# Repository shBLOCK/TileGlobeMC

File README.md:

# TileGlobeMC

-----

[Demo Video](https://youtu.be/YhDgAMrMPlI)

TODO: Description

Project Structure
-----
- tileglobe: game logic
- datagen/mod: a fabric modding environment for extracting/generating data from vanilla (e.g. blockstate info, networking packet IDs, etc.)
- tileglobe_pymeta: Python environment and helper package for [pymeta](https://github.com/shBLOCK/pymeta) usage in the project
- tileglobe_server: Minecraft server protocol implementation
- tileglobe_runtime: runtime platform implementation
  - pc
  - rp2350: runnable on a [Pimoroni Pico Plus 2 W](https://shop.pimoroni.com/en-us/products/pimoroni-pico-plus-2-w)

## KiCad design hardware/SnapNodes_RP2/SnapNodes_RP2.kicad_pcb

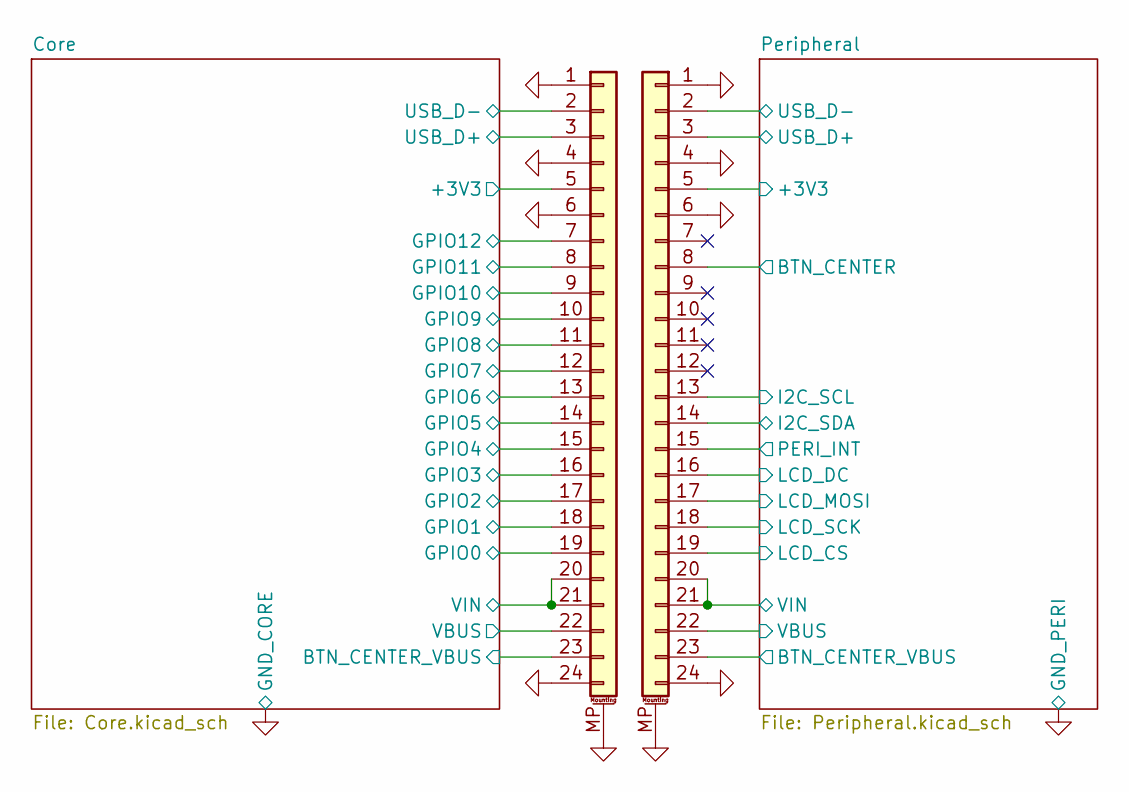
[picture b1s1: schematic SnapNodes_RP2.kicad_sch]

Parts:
J20, J21: Conn_01x24_MountingPin; FPC_Verticle_24pin_0.5mm

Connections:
+3V3: J20.5; also elsewhere on the board
/Core/BTN_CENTER_VBUS: J20.23; also elsewhere on the board
/Core/GPIO0: J20.19; also elsewhere on the board
/Core/GPIO1: J20.18; also elsewhere on the board
/Core/GPIO2: J20.17; also elsewhere on the board
/Core/GPIO3: J20.16; also elsewhere on the board
/Core/GPIO4: J20.15; also elsewhere on the board
/Core/GPIO5: J20.14; also elsewhere on the board
/Core/GPIO6: J20.13; also elsewhere on the board
/Core/GPIO7: J20.12; also elsewhere on the board
/Core/GPIO8: J20.11; also elsewhere on the board
/Core/GPIO9: J20.10; also elsewhere on the board
/Core/GPIO10: J20.9; also elsewhere on the board
/Core/GPIO11: J20.8; also elsewhere on the board
/Core/GPIO12: J20.7; also elsewhere on the board
/Core/USB_D+: J20.3; also elsewhere on the board
/Core/USB_D-: J20.2; also elsewhere on the board
/Core/VIN: J20.20, J20.21; also elsewhere on the board
/Peripheral/+3V3: J21.5; also elsewhere on the board
/Peripheral/BTN_CENTER: J21.8; also elsewhere on the board
/Peripheral/BTN_CENTER_VBUS: J21.23; also elsewhere on the board
/Peripheral/I2C_SCL: J21.13; also elsewhere on the board
/Peripheral/I2C_SDA: J21.14; also elsewhere on the board
/Peripheral/LCD_CS: J21.19; also elsewhere on the board
/Peripheral/LCD_DC: J21.16; also elsewhere on the board
/Peripheral/LCD_MOSI: J21.17; also elsewhere on the board
/Peripheral/LCD_SCK: J21.18; also elsewhere on the board
/Peripheral/PERI_INT: J21.15; also elsewhere on the board
/Peripheral/USB_D+: J21.3; also elsewhere on the board
/Peripheral/USB_D-: J21.2; also elsewhere on the board
/Peripheral/VBUS: J21.22; also elsewhere on the board
/Peripheral/VIN: J21.20, J21.21; also elsewhere on the board
GND_CORE: J20.1, J20.4, J20.6, J20.24, J20.MP (MountPin); also elsewhere on the board
GND_PERI: J21.1, J21.4, J21.6, J21.24, J21.MP (MountPin); also elsewhere on the board
VBUS: J20.22; also elsewhere on the board

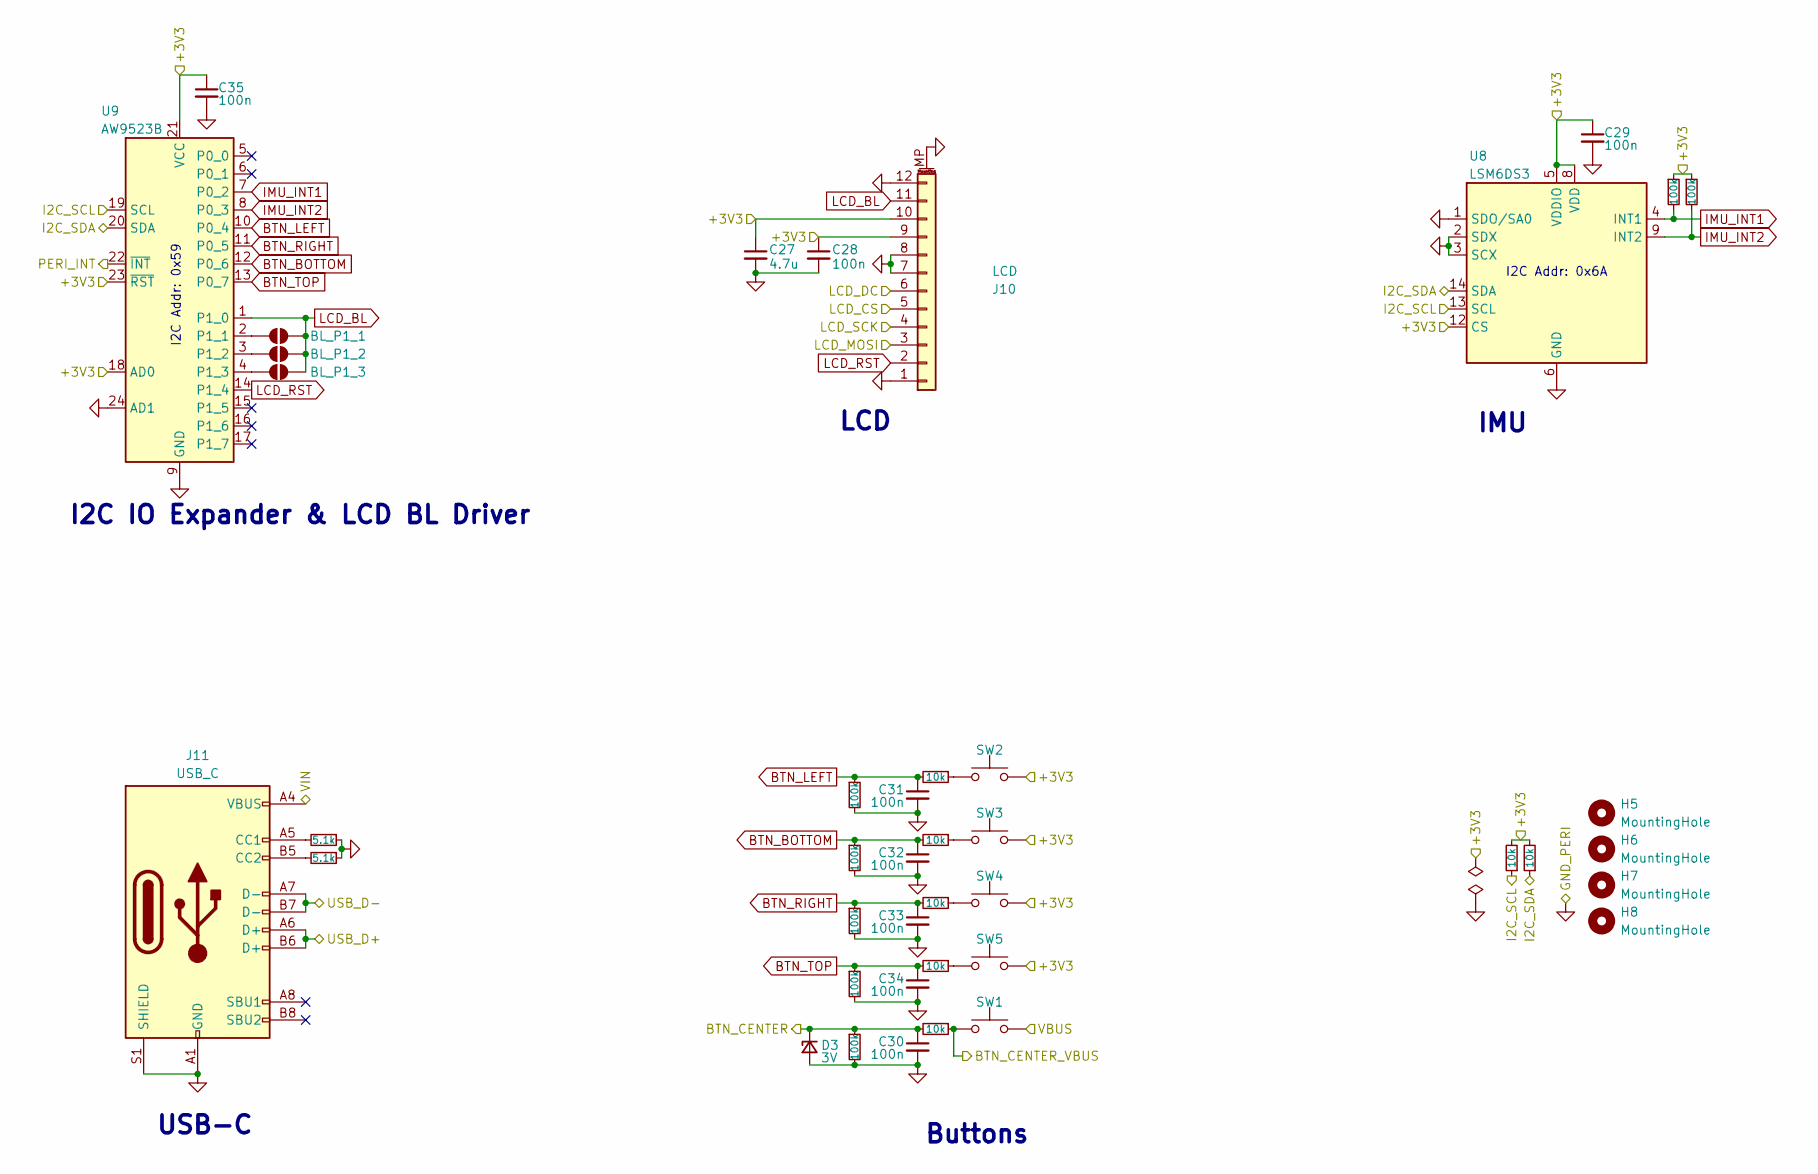
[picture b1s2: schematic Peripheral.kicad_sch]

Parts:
C27: 4.7u; C_0603_1608Metric
C28, C29, C30, C31, C32, C33, C34, C35: 100n; C_0603_1608Metric
D3: 3V; D_SOD-523
H5, H6, H7, H8: MountingHole; MountingHole_2.2mm_M2
J10: LCD; TE_1-1734839-2_1x12-1MP_P0.5mm_Horizontal
J11: USB_C; USB_C_Receptacle_GCT_USB4105-xx-A_16P_TopMnt_Horizontal
JP3: BL_P1_1; SolderJumper-2_P1.3mm_Open_TrianglePad1.0x1.5mm
JP4: BL_P1_2; SolderJumper-2_P1.3mm_Open_TrianglePad1.0x1.5mm
JP5: BL_P1_3; SolderJumper-2_P1.3mm_Open_TrianglePad1.0x1.5mm
R31, R42, R43, R44, R45, R46, R47: 100k; R_0603_1608Metric
R32, R33: 5.1k; R_0603_1608Metric
R35, R36, R37, R38, R39, R40, R41: 10k; R_0603_1608Metric
SW1: Center; SW_SPST_PTS647_Sx38
SW2: Left; SW_SPST_PTS647_Sx38
SW3: Bottom; SW_SPST_PTS647_Sx38
SW4: Right; SW_SPST_PTS647_Sx38
SW5: Top; SW_SPST_PTS647_Sx38
U8: LSM6DS3; LGA-14_3x2.5mm_P0.5mm_LayoutBorder3x4y
U9: AW9523B; QFN-24-1EP_4x4mm_P0.5mm_EP2.7x2.7mm

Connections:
/Peripheral/+3V3: C27.1, C28.1, C29.1, C35.1, J10.9, J10.10, R36.2, R37.2, R46.1, R47.1, SW2.2, SW3.2, SW4.2, SW5.2, U8.5 (VDDIO), U8.8 (VDD), U8.12 (CS), U9.18 (AD0), U9.21 (VCC), U9.23 (~RST); also elsewhere on the board
/Peripheral/BTN_CENTER: C30.1, D3.1 (K), R35.2, R45.1; also elsewhere on the board
/Peripheral/BTN_CENTER_VBUS: R35.1, SW1.1; also elsewhere on the board
/Peripheral/I2C_SCL: R36.1, U8.13 (SCL), U9.19 (SCL); also elsewhere on the board
/Peripheral/I2C_SDA: R37.1, U8.14 (SDA), U9.20 (SDA); also elsewhere on the board
/Peripheral/LCD_CS: J10.5; also elsewhere on the board
/Peripheral/LCD_DC: J10.6; also elsewhere on the board
/Peripheral/LCD_MOSI: J10.3; also elsewhere on the board
/Peripheral/LCD_SCK: J10.4; also elsewhere on the board
/Peripheral/PERI_INT: U9.22 (~INT); also elsewhere on the board
/Peripheral/USB_D+: J11.A6 (D+), J11.B6 (D+); also elsewhere on the board
/Peripheral/USB_D-: J11.A7 (D-), J11.B7 (D-); also elsewhere on the board
/Peripheral/VBUS: SW1.2; also elsewhere on the board
/Peripheral/VIN: J11.A4 (VBUS), J11.A9 (VBUS), J11.B4 (VBUS), J11.B9 (VBUS); also elsewhere on the board
BTN_BOTTOM: C32.1, R39.2, R42.1, U9.12 (P0_6)
BTN_LEFT: C31.1, R31.1, R38.2, U9.10 (P0_4)
BTN_RIGHT: C33.1, R40.2, R43.1, U9.11 (P0_5)
BTN_TOP: C34.1, R41.2, R44.1, U9.13 (P0_7)
GND_PERI: C27.2, C28.2, C29.2, C30.2, C31.2, C32.2, C33.2, C34.2, C35.2, D3.2 (A), J10.1, J10.7, J10.8, J10.12, J10.MP (MountPin), J11.A1 (GND), J11.A12 (GND), J11.B1 (GND), J11.B12 (GND), J11.S1 (SHIELD), R31.2, R32.1, R33.1, R42.2, R43.2, R44.2, R45.2, U8.1 (SDO/SA0), U8.2 (SDX), U8.3 (SCX), U8.6 (GND), U8.7 (GND), U9.9 (GND), U9.24 (AD1), U9.25 (GND); also elsewhere on the board
IMU_INT1: R46.2, U8.4 (INT1), U9.7 (P0_2)
IMU_INT2: R47.2, U8.9 (INT2), U9.8 (P0_3)
LCD_BL: J10.11, JP3.2 (B), JP4.2 (B), JP5.2 (B), U9.1 (P1_0)
LCD_RST: J10.2, U9.14 (P1_4)
unnamed: J11.A5 (CC1), R33.2
unnamed: J11.B5 (CC2), R32.2
unnamed: JP3.1 (A), U9.2 (P1_1)
unnamed: JP4.1 (A), U9.3 (P1_2)
unnamed: JP5.1 (A), U9.4 (P1_3)
unnamed: R38.1, SW2.1
unnamed: R39.1, SW3.1
unnamed: R40.1, SW4.1
unnamed: R41.1, SW5.1

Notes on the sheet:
IMU
I2C Addr: 0x59
I2C Addr: 0x6A
I2C IO Expander & LCD BL Driver
LCD
Buttons
USB-C

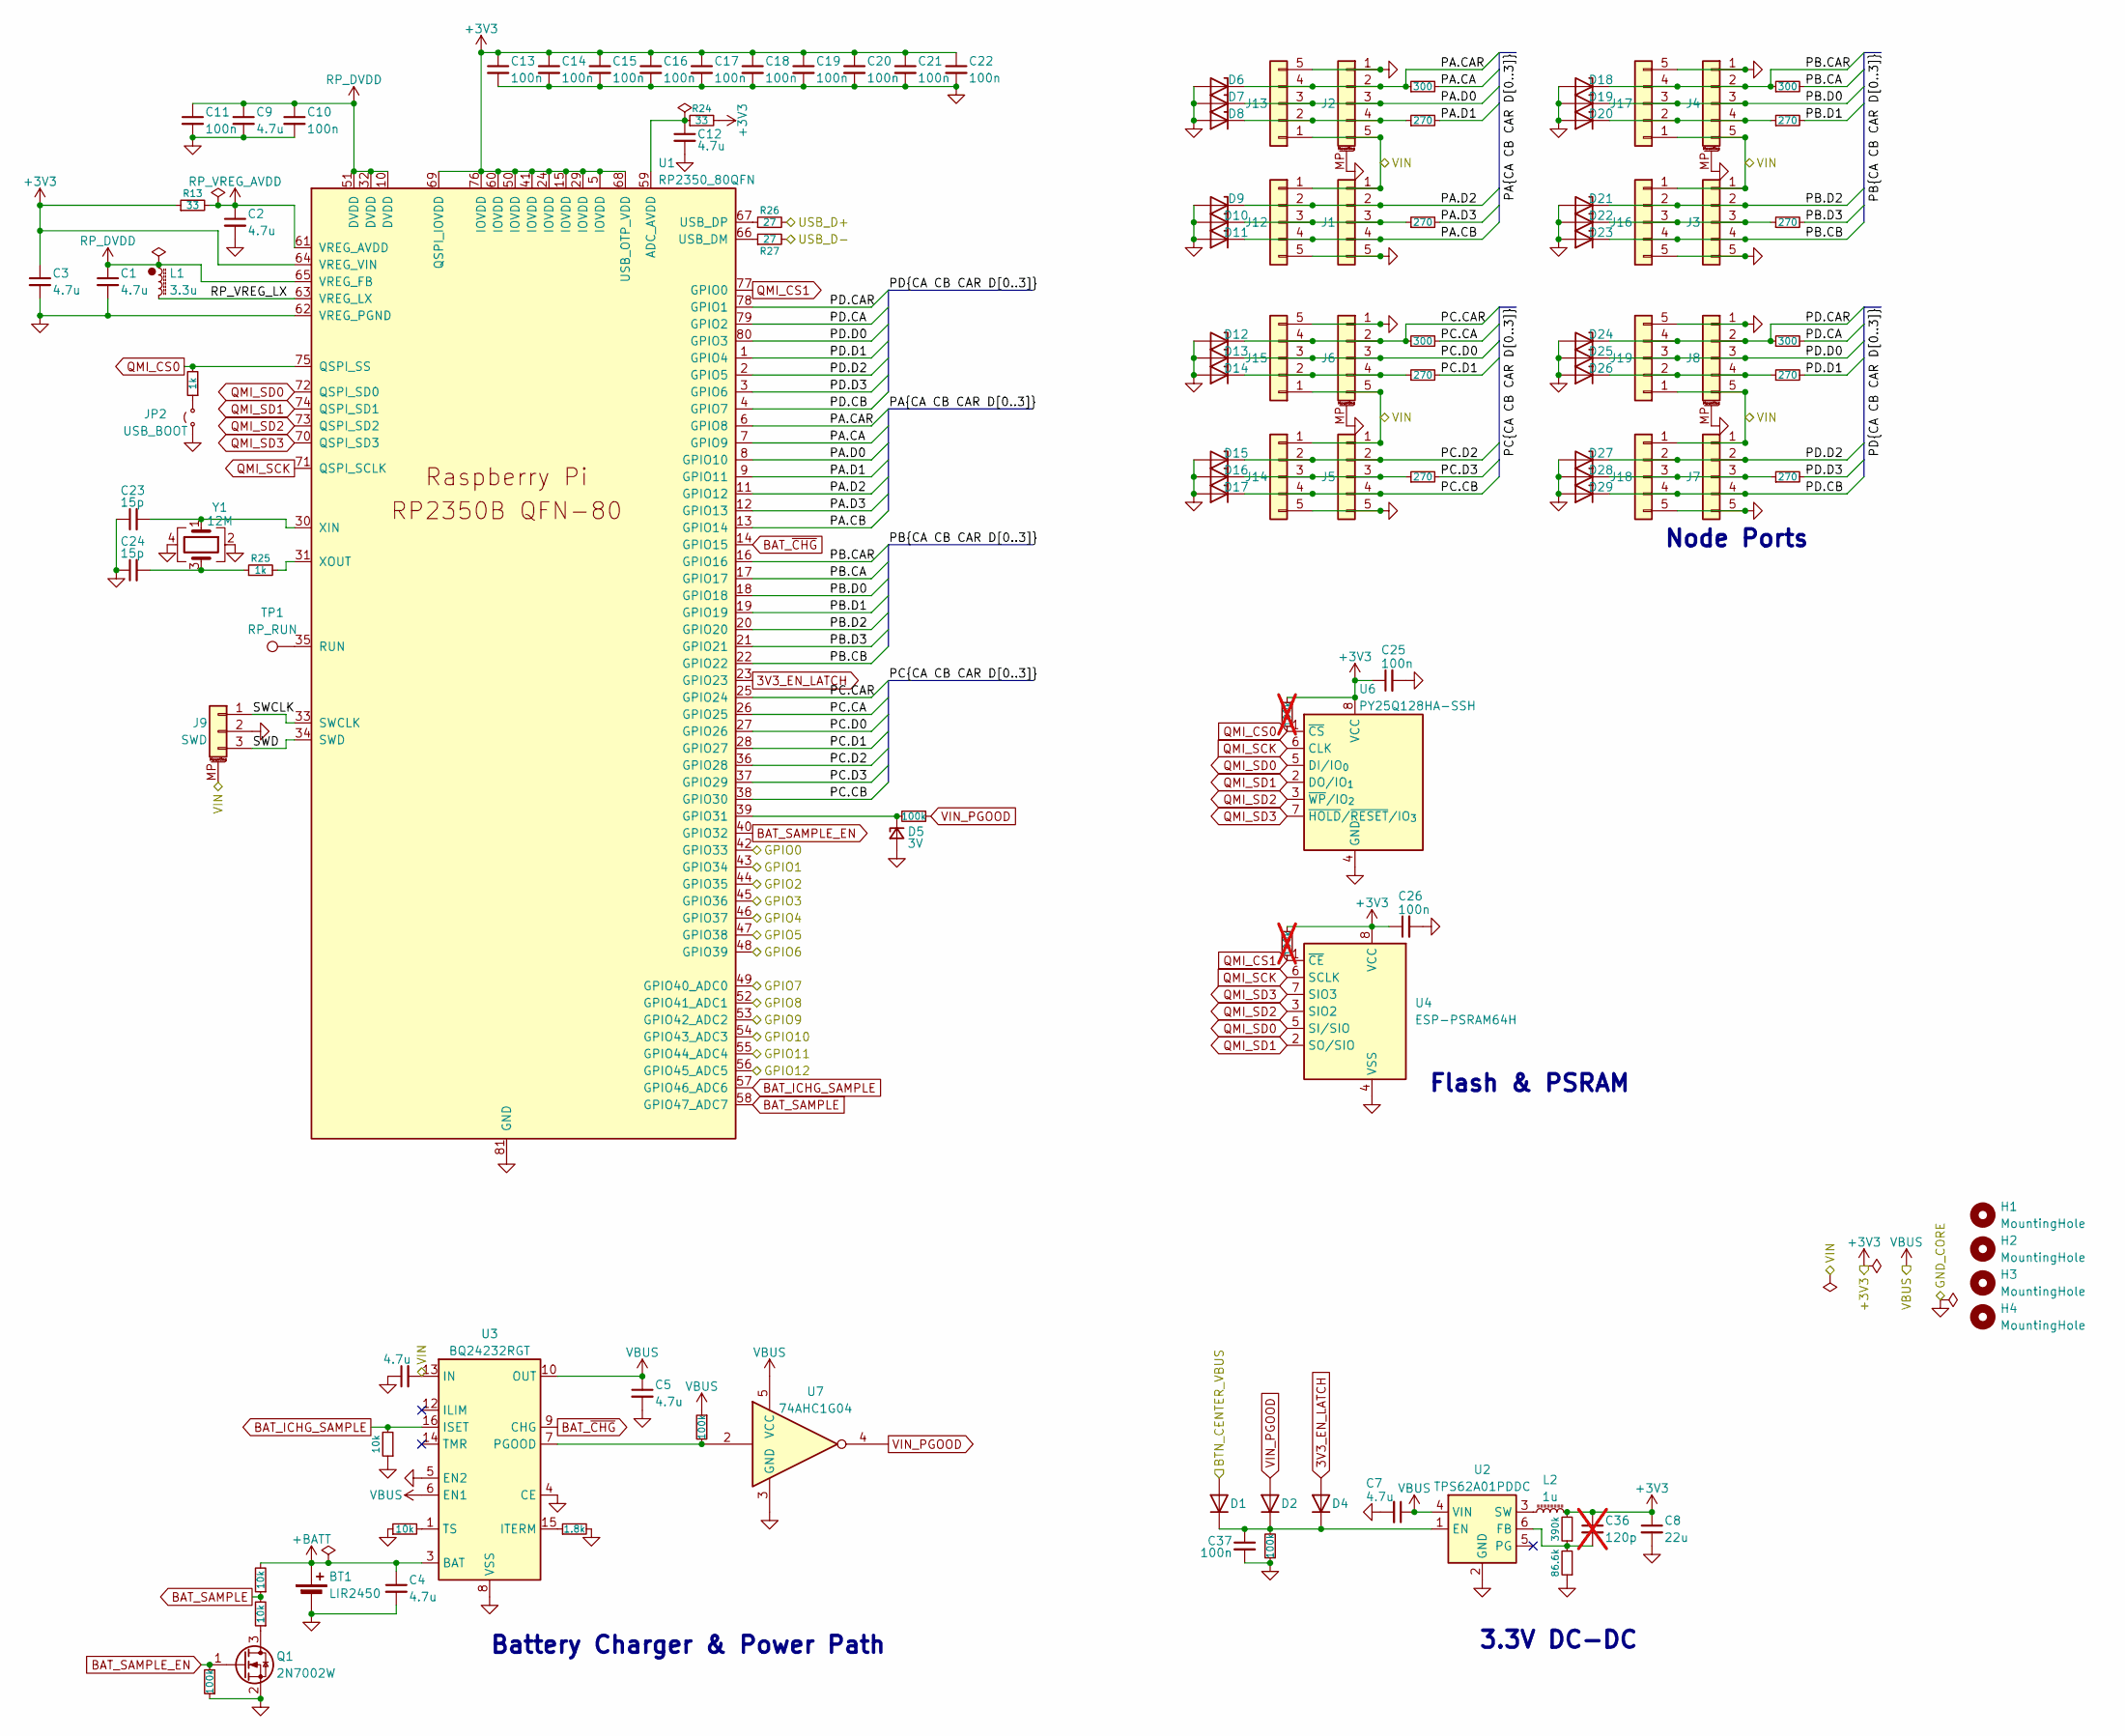
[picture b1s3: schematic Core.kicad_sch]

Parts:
BT1: LIR2450; BS-24-B___014
C1, C2, C3, C9, C12: 4.7u; C_0402_1005Metric
C4, C5, C6, C7: 4.7u; C_0603_1608Metric
C8: 22u; C_0603_1608Metric
C10, C11, C13, C14, C15, C16, C17, C18, C19, C20, C21, C22, C25, C26: 100n; C_0402_1005Metric
C23, C24: 15p; C_0402_1005Metric
C36: 120p; C_0402_1005Metric; not fitted
C37: 100n; C_0603_1608Metric
D1, D2, D4: 1N4148WT; D_SOD-523
D5: 3V; D_SOD-523
D6, D7, D8, D9, D10, D11, D12, D13, D14, D15, D16, D17, D18, D19, D20, D21, D22, D23, D24, D25, D26, D27, D28, D29: ESD5Z3.3-HXY; D_SOD-523
H1, H2, H3, H4: MountingHole; MountingHole_2.2mm_M2
J1, J3, J5, J7: P_Female; BC-20-5PD160
J2, J4, J6, J8: P_Male; BC-15-5P380
J9: SWD; JST_SH_BM03B-SRSS-TB_1x03-1MP_P1.00mm_Vertical
J12, J14, J16, J18: P_Female_Fallback; PinSocket_1x05_P2.54mm_Horizontal_NoSilk
J13, J15, J17, J19: P_Male_Fallback; PinHeader_1x05_P2.54mm_Horizontal_NoSilk
JP2: USB_BOOT; PinHeader_1x02_P1.00mm_Vertical
L1: 3.3u; L_pol_2016
L2: 1u; L_Wuerth_MAPI-2010
Q1: 2N7002W; SOT-323_SC-70
R1, R4, R7, R10: 300; R_0603_1608Metric
R2, R3, R5, R6, R8, R9, R11, R12: 270; R_0603_1608Metric
R13, R24: 33; R_0402_1005Metric
R14, R15: 10k; R_0603_1608Metric
R16: 1.8k; R_0603_1608Metric
R17, R18: 10k; R_0402_1005Metric
R19, R22, R23: 100k; R_0402_1005Metric
R20: 86.6k; R_0402_1005Metric
R21: 390k; R_0402_1005Metric
R25: 1k; R_0402_1005Metric
R26, R27: 27; R_0402_1005Metric
R28, R29: 100k; R_0603_1608Metric; not fitted
R30: 1k; R_0603_1608Metric
R34: 100k; R_0603_1608Metric
TP1: RP_RUN; TestPoint_THTPad_D1.0mm_Drill0.5mm
U1: RP2350_80QFN; RP2350-QFN-80-1EP_10x10_P0.4mm_EP3.4x3.4mm_ThermalVias
U2: TPS62A01PDDC; SOT-23-6
U3: BQ24232RGT; VQFN-16-1EP_3x3mm_P0.5mm_EP1.68x1.68mm_ThermalVias
U4: ESP-PSRAM64H; SOIC-8_3.9x4.9mm_P1.27mm
U6: PY25Q128HA-SSH; SOIC-8_5.3x5.3mm_P1.27mm
U7: 74AHC1G04; SOT-353_SC-70-5
Y1: 12M; Crystal_SMD_3225-4Pin_3.2x2.5mm

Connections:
3V3_EN_LATCH: D4.2 (A), U1.23 (GPIO23)
+3V3: C3.1, C8.1, C13.1, C14.1, C15.1, C16.1, C17.1, C18.1, C19.1, C20.1, C21.1, C22.1, C25.1, C26.1, C36.1, L2.2, R13.1, R21.2, R24.2, R28.2, R29.2, U1.5 (IOVDD), U1.15 (IOVDD), U1.24 (IOVDD), U1.29 (IOVDD), U1.41 (IOVDD), U1.50 (IOVDD), U1.60 (IOVDD), U1.64 (VREG_VIN), U1.68 (USB_OTP_VDD), U1.69 (QSPI_IOVDD), U1.76 (IOVDD), U4.8 (VCC), U6.8 (VCC); also elsewhere on the board
+BATT: BT1.1 (+), C4.1, R18.2, U3.2 (BAT), U3.3 (BAT)
/Core/BTN_CENTER_VBUS: D1.2 (A); also elsewhere on the board
/Core/GPIO0: U1.42 (GPIO33); also elsewhere on the board
/Core/GPIO1: U1.43 (GPIO34); also elsewhere on the board
/Core/GPIO2: U1.44 (GPIO35); also elsewhere on the board
/Core/GPIO3: U1.45 (GPIO36); also elsewhere on the board
/Core/GPIO4: U1.46 (GPIO37); also elsewhere on the board
/Core/GPIO5: U1.47 (GPIO38); also elsewhere on the board
/Core/GPIO6: U1.48 (GPIO39); also elsewhere on the board
/Core/GPIO7: U1.49 (GPIO40_ADC0); also elsewhere on the board
/Core/GPIO8: U1.52 (GPIO41_ADC1); also elsewhere on the board
/Core/GPIO9: U1.53 (GPIO42_ADC2); also elsewhere on the board
/Core/GPIO10: U1.54 (GPIO43_ADC3); also elsewhere on the board
/Core/GPIO11: U1.55 (GPIO44_ADC4); also elsewhere on the board
/Core/GPIO12: U1.56 (GPIO45_ADC5); also elsewhere on the board
/Core/PA.CA: R1.2, U1.7 (GPIO9)
/Core/PA.CAR: D6.1 (K), J2.2, J13.4, R1.1, U1.6 (GPIO8)
/Core/PA.CB: D11.1 (K), J1.4, J12.4, U1.13 (GPIO14)
/Core/PA.D0: D7.1 (K), J2.3, J13.3, U1.8 (GPIO10)
/Core/PA.D1: R2.2, U1.9 (GPIO11)
/Core/PA.D2: D9.1 (K), J1.2, J12.2, U1.11 (GPIO12)
/Core/PA.D3: R3.2, U1.12 (GPIO13)
/Core/PB.CA: R4.2, U1.17 (GPIO17)
/Core/PB.CAR: D18.1 (K), J4.2, J17.4, R4.1, U1.16 (GPIO16)
/Core/PB.CB: D23.1 (K), J3.4, J16.4, U1.22 (GPIO22)
/Core/PB.D0: D19.1 (K), J4.3, J17.3, U1.18 (GPIO18)
/Core/PB.D1: R5.2, U1.19 (GPIO19)
/Core/PB.D2: D21.1 (K), J3.2, J16.2, U1.20 (GPIO20)
/Core/PB.D3: R6.2, U1.21 (GPIO21)
/Core/PC.CA: R7.2, U1.26 (GPIO25)
/Core/PC.CAR: D12.1 (K), J6.2, J15.4, R7.1, U1.25 (GPIO24)
/Core/PC.CB: D17.1 (K), J5.4, J14.4, U1.38 (GPIO30)
/Core/PC.D0: D13.1 (K), J6.3, J15.3, U1.27 (GPIO26)
/Core/PC.D1: R8.2, U1.28 (GPIO27)
/Core/PC.D2: D15.1 (K), J5.2, J14.2, U1.36 (GPIO28)
/Core/PC.D3: R9.2, U1.37 (GPIO29)
/Core/PD.CA: R10.2, U1.79 (GPIO2)
/Core/PD.CAR: D24.1 (K), J8.2, J19.4, R10.1, U1.78 (GPIO1)
/Core/PD.CB: D29.1 (K), J7.4, J18.4, U1.4 (GPIO7)
/Core/PD.D0: D25.1 (K), J8.3, J19.3, U1.80 (GPIO3)
/Core/PD.D1: R11.2, U1.1 (GPIO4)
/Core/PD.D2: D27.1 (K), J7.2, J18.2, U1.2 (GPIO5)
/Core/PD.D3: R12.2, U1.3 (GPIO6)
/Core/RP_VREG_LX: L1.2, U1.63 (VREG_LX)
/Core/SWCLK: J9.1, U1.33 (SWCLK)
/Core/SWD: J9.3, U1.34 (SWD)
/Core/USB_D+: R26.2; also elsewhere on the board
/Core/USB_D-: R27.2; also elsewhere on the board
/Core/VIN: C6.2, J1.1, J2.5, J3.1, J4.5, J5.1, J6.5, J7.1, J8.5, J9.MP (MountPin), J12.1, J13.1, J14.1, J15.1, J16.1, J17.1, J18.1, J19.1, U3.13 (IN); also elsewhere on the board
BAT_ICHG_SAMPLE: R15.2, U1.57 (GPIO46_ADC6), U3.16 (ISET)
BAT_SAMPLE: R17.2, R18.1, U1.58 (GPIO47_ADC7)
BAT_SAMPLE_EN: Q1.1 (G), R19.2, U1.40 (GPIO32)
BAT_~CHG: U1.14 (GPIO15), U3.9 (CHG)
GND_CORE: BT1.2 (-), C1.2, C2.2, C3.2, C4.2, C5.2, C6.1, C7.2, C8.2, C9.2, C10.2, C11.2, C12.2, C13.2, C14.2, C15.2, C16.2, C17.2, C18.2, C19.2, C20.2, C21.2, C22.2, C23.1, C24.1, C25.2, C26.2, C37.2, D5.2 (A), D6.2 (A), D7.2 (A), D8.2 (A), D9.2 (A), D10.2 (A), D11.2 (A), D12.2 (A), D13.2 (A), D14.2 (A), D15.2 (A), D16.2 (A), D17.2 (A), D18.2 (A), D19.2 (A), D20.2 (A), D21.2 (A), D22.2 (A), D23.2 (A), D24.2 (A), D25.2 (A), D26.2 (A), D27.2 (A), D28.2 (A), D29.2 (A), J1.5, J2.1, J2.MP (MountPin), J3.5, J4.1, J4.MP (MountPin), J5.5, J6.1, J6.MP (MountPin), J7.5, J8.1, J8.MP (MountPin), J9.2, J12.5, J13.5, J14.5, J15.5, J16.5, J17.5, J18.5, J19.5, JP2.1 (A), Q1.2 (S), R14.1, R15.1, R16.2, R19.1, R20.1, R34.1, U1.62 (VREG_PGND), U1.81 (GND), U2.2 (GND), U3.4 (CE), U3.5 (EN2), U3.8 (VSS), U3.17 (VSS), U4.4 (VSS), U6.4 (GND), U7.3 (GND), Y1.2, Y1.4; also elsewhere on the board
unnamed: C24.2, R25.1, Y1.3
unnamed: C37.1, D1.1 (K), D2.1 (K), D4.1 (K), R34.2, U2.1 (EN)
unnamed: D5.1 (K), R23.2, U1.39 (GPIO31)
unnamed: D8.1 (K), J2.4, J13.2, R2.1
unnamed: D10.1 (K), J1.3, J12.3, R3.1
unnamed: D14.1 (K), J6.4, J15.2, R8.1
unnamed: D16.1 (K), J5.3, J14.3, R9.1
unnamed: D20.1 (K), J4.4, J17.2, R5.1
unnamed: D22.1 (K), J3.3, J16.3, R6.1
unnamed: D26.1 (K), J8.4, J19.2, R11.1
unnamed: D28.1 (K), J7.3, J18.3, R12.1
unnamed: JP2.2 (B), R30.1
unnamed: Q1.3 (D), R17.1
unnamed: C12.1, R24.1, U1.59 (ADC_AVDD)
unnamed: TP1.1, U1.35 (RUN)
unnamed: R27.1, U1.66 (USB_DM)
unnamed: R26.1, U1.67 (USB_DP)
unnamed: C23.2, U1.30 (XIN), Y1.1
unnamed: R25.2, U1.31 (XOUT)
unnamed: C36.2, R20.2, R21.1, U2.6 (FB)
unnamed: L2.1, U2.3 (SW)
unnamed: R16.1, U3.15 (ITERM)
unnamed: R22.2, U3.7 (PGOOD), U7.2
unnamed: R14.2, U3.1 (TS)
QMI_CS0: R28.1, R30.2, U1.75 (QSPI_SS), U6.1 (~CS)
QMI_CS1: R29.1, U1.77 (GPIO0), U4.1 (~CE)
QMI_SCK: U1.71 (QSPI_SCLK), U4.6 (SCLK), U6.6 (CLK)
QMI_SD0: U1.72 (QSPI_SD0), U4.5 (SI/SIO), U6.5 (DI/IO_{0})
QMI_SD1: U1.74 (QSPI_SD1), U4.2 (SO/SIO), U6.2 (DO/IO_{1})
QMI_SD2: U1.73 (QSPI_SD2), U4.3 (SIO2), U6.3 (~WP/IO_{2})
QMI_SD3: U1.70 (QSPI_SD3), U4.7 (SIO3), U6.7 (~HOLD/~RESET/IO_{3})
RP_DVDD: C1.1, C9.1, C10.1, C11.1, L1.1, U1.10 (DVDD), U1.32 (DVDD), U1.51 (DVDD), U1.65 (VREG_FB)
RP_VREG_AVDD: C2.1, R13.2, U1.61 (VREG_AVDD)
VBUS: C5.1, C7.1, R22.1, U2.4 (VIN), U3.6 (EN1), U3.10 (OUT), U3.11 (OUT), U7.5 (VCC); also elsewhere on the board
VIN_PGOOD: D2.2 (A), R23.1, U7.4

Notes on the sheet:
Node Ports
Battery Charger & Power Path
3.3V DC-DC
Flash & PSRAM

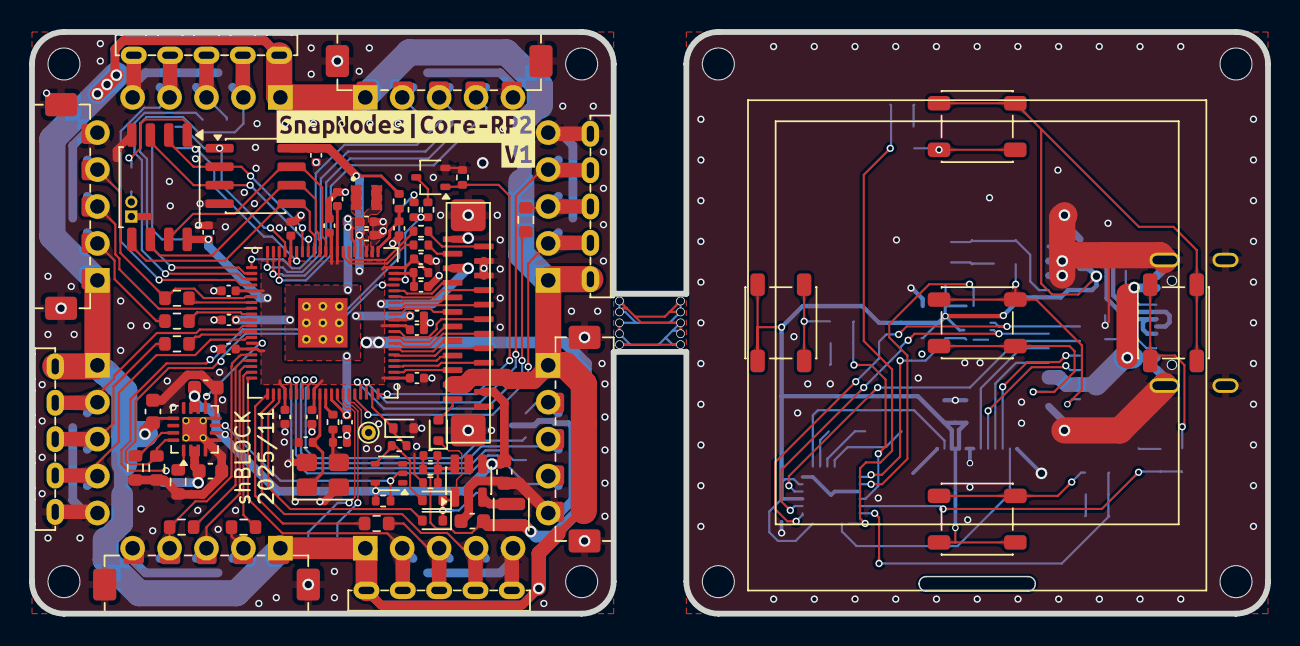
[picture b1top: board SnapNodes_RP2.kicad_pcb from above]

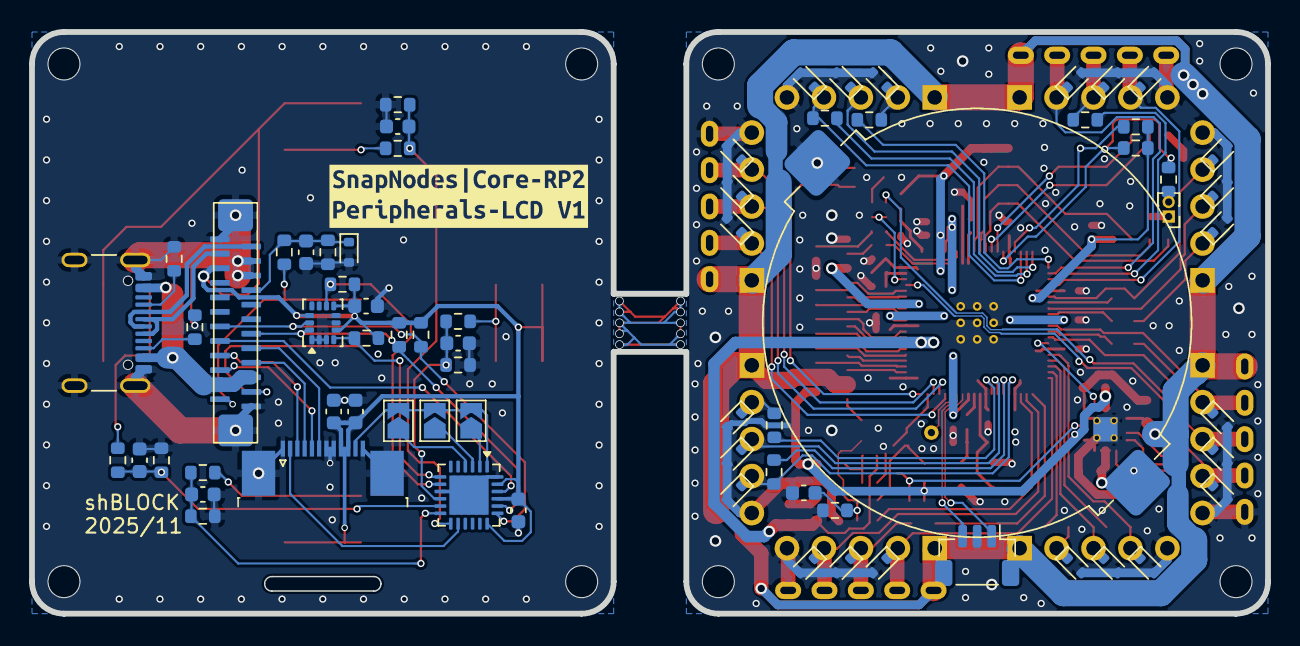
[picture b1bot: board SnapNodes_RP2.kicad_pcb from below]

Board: 2 copper layers, 85.0 x 40.0 mm, 168 parts (72 on the bottom side), 123 nets.

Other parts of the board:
kibuzzard-6913C2AE: G***; kibuzzard-6913C2AE
kibuzzard-6913C792: G***; kibuzzard-6913C792
kibuzzard-69136CB0: G***; kibuzzard-69136CB0

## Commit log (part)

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2025-10-29 Commit before switching to std socket on PC
2025-10-30 RP2350 blinky
2025-11-02 PCB progress
2025-11-03 Login achieved!
2025-11-06 Commit before switching to multi board design
2025-11-10 Main PCB progress
2025-11-10 Main PCB done
2025-11-11 PCB done
2025-11-11 BOM; PCB minor tweaks
2025-11-11 Rename PCB project to SnapNodes-RP2
2025-11-12 PCB minor changes
2025-11-14 Add Embassy as git submodule
2025-11-14 Many changes. MC server working on RP2350B with CYW43!
2025-11-16 Minecraft blocks datagen
2025-11-23 Cad progress
2025-11-23 Cad finished
2025-11-25 Cad fixes
2025-11-25 Rename `client` folder to `neoforge`; blocks datagen
2025-11-25 Add cad/.idea to gitignore
2025-11-25 Proc macro basics
2025-11-27 Progress
2025-12-01 Progress save cuz I don't trust this crappy laptop with the soldered SSD
2025-12-02 Update embassy
2025-12-03 Downgrade embassy: https://github.com/embassy-rs/embassy/issues/4977
2025-12-04 I give up, cursed unsafe casts yay!
2025-12-07 Redstone!!!
2025-12-07 More Redstone!!!
2025-12-08 Redstone lamp
2025-12-08 Performance hack & overclock
2025-12-09 Commit message
2025-12-13 Adafruit FruitJam platform
